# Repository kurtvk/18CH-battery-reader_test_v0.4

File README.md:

# 18CH-battery-reader_test_v0.4
18CH battery reader_test_v0.4

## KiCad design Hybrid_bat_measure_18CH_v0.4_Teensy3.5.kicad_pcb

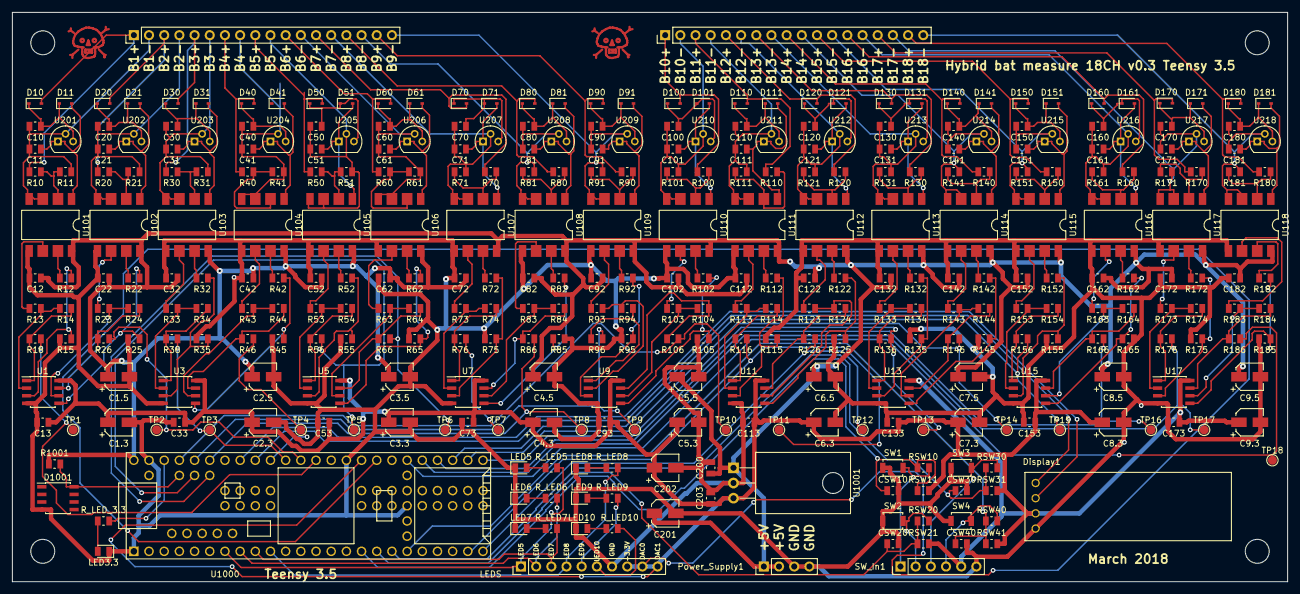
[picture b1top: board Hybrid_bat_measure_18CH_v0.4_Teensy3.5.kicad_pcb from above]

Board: 2 copper layers, 213.4 x 95.2 mm, 356 parts (0 on the bottom side), 228 nets.

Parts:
C1.3, C1.5, C2.3, C2.5, C3.3, C3.5, C4.3, C4.5, C5.3, C5.5, C6.3, C6.5, C7.3, C7.5, C8.3, C8.5, C9.3, C9.5, C201, C202: 10uF; CP_Elec_4x5.3
C10, C11, C12, C13, C20, C21, C22, C30, C31, C32, C33, C40, C41, C42, C50, C51, C52, C53, C60, C61, C62, C70, C71, C72, C73, C80, C81, C82, C90, C91, C92, C93, C100, C101, C102, C110, C111, C112, C113, C120, C121, C122, C130, C131, C132, C133, C140, C141, C142, C150, C151, C152, C153, C160, C161, C162, C170, C171, C172, C173, C180, C181, C182, C200, C203: 100n; C_0805_2012Metric
CSW10, CSW20, CSW30, CSW40: 100n; C_0805_2012Metric
D10, D11, D20, D21, D30, D31, D40, D41, D50, D51, D60, D61, D70, D71, D80, D81, D90, D91, D100, D101, D110, D111, D120, D121, D130, D131, D140, D141, D150, D151, D160, D161, D170, D171, D180, D181: D; D_SOD-323
D1001: LM385D-2.5; SOIC-8_3.9x4.9mm_P1.27mm
Display1: SSD1306; SSD1306_OLED
Inputs1, Inputs2: Conn_01x18; PinHeader_1x18_P2.54mm_Vertical
LED3.3: LED 3.3V Teensy; LED_0805_2012Metric
LED5: LED 5; LED_0805_2012Metric
LED6: LED 6; LED_0805_2012Metric
LED7: LED 7; LED_0805_2012Metric
LED8: LED 8; LED_0805_2012Metric
LED9: LED 9; LED_0805_2012Metric
LED10: LED 10; LED_0805_2012Metric
LEDS: Conn_01x10; PinHeader_1x10_P2.54mm_Vertical
MK1, MK2, MK3, MK4: Mounting_Hole_PAD; MountingHole_4mm
Power_Supply1: Conn_01x04; PinHeader_1x04_P2.54mm_Vertical
R10, R20, R30, R40, R50, R60, R70, R80, R90, R100, R110, R120, R130, R140, R150, R160, R170, R180: 15k; R_0805_2012Metric
R11, R21, R31, R41, R51, R61, R71, R81, R91, R101, R111, R121, R131, R141, R151, R161, R171, R181: 200; R_0805_2012Metric
R12, R13, R14, R15, R22, R23, R24, R25, R32, R33, R34, R35, R42, R43, R44, R45, R52, R53, R54, R55, R62, R63, R64, R65, R72, R73, R74, R75, R82, R83, R84, R85, R92, R93, R94, R95, R102, R103, R104, R105, R112, R113, R114, R115, R122, R123, R124, R125, R132, R133, R134, R135, R142, R143, R144, R145, R152, R153, R154, R155, R162, R163, R164, R165, R172, R173, R174, R175, R182, R183, R184, R185, R1001: 10k; R_0805_2012Metric
R16, R26, R36, R46, R56, R66, R76, R86, R96, R106, R116, R126, R136, R146, R156, R166, R176, R186: 1k; R_0805_2012Metric
RSW10, RSW20, RSW30, RSW40: 1k; R_0805_2012Metric
RSW11, RSW21, RSW31, RSW41: 10k; R_0805_2012Metric
R_LED5, R_LED6, R_LED7, R_LED8, R_LED9, R_LED10: 1k; R_0805_2012Metric
R_LED_3.3: 1k; R_0805_2012Metric
SKULL1, SKULL2: Symbol_Danger_CopperTop_Small
SW1, SW2, SW3, SW4: SW_Push; SW_SPST_B3U-1000P
SW_In1: Conn_01x06; PinHeader_1x06_P2.54mm_Vertical
TP1, TP2, TP3, TP4, TP5, TP6, TP7, TP8, TP9, TP10, TP11, TP12, TP13, TP14, TP15, TP16, TP17, TP18: Test Point; TestPoint_Pad_D1.5mm
U1, U3, U5, U7, U9, U11, U13, U15, U17: OPA2209; SOIC-8_3.9x4.9mm_P1.27mm
U101, U102, U103, U104, U105, U106, U107, U108, U109, U110, U111, U112, U113, U114, U115, U116, U117, U118: HCPL-7800; Fairchild_LSOP-8
U201, U202, U203, U204, U205, U206, U207, U208, U209, U210, U211, U212, U213, U214, U215, U216, U217, U218: MC78L05_TO92; TO-92
U1000: Teensy3.5; Teensy35_36
U1001: LM78_3.3; TO-220-3_Horizontal

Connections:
+3V3: C1.3.1, C2.3.1, C3.3.1, C4.3.1, C5.3.1, C6.3.1, C7.3.1, C8.3.1, C9.3.1, C13.1, C33.1, C53.1, C73.1, C93.1, C113.1, C133.1, C153.1, C173.1, C202.1, C203.1, Display1.2, LEDS.8, RSW11.2, RSW21.2, RSW31.2, RSW41.2, SW_In1.5, U1.8, U3.8, U5.8, U7.8, U9.8, U11.8, U13.8, U15.8, U17.8, U1001.3
+5V: C1.5.1, C2.5.1, C3.5.1, C4.5.1, C5.5.1, C6.5.1, C7.5.1, C8.5.1, C9.5.1, C12.1, C22.1, C32.1, C42.1, C52.1, C62.1, C72.1, C82.1, C92.1, C102.1, C112.1, C122.1, C132.1, C142.1, C152.1, C162.1, C172.1, C182.1, C200.1, C201.1, Power_Supply1.1, Power_Supply1.2, R1001.1, U101.8, U102.8, U103.8, U104.8, U105.8, U106.8, U107.8, U108.8, U109.8, U110.8, U111.8, U112.8, U113.8, U114.8, U115.8, U116.8, U117.8, U118.8, U1000.53, U1001.1
B1+: D10.2, Inputs1.1, R10.2
B1-: C10.2, C11.2, Inputs1.2, R11.1, U101.3, U101.4, U201.2
B1_output: R16.1, TP1.1, U1000.41
B2+: D20.2, Inputs1.3, R20.2
B2-: C20.2, C21.2, Inputs1.4, R21.1, U102.3, U102.4, U202.2
B2_output: R26.1, TP2.1, U1000.42
B3+: D30.2, Inputs1.5, R30.2
B3-: C30.2, C31.2, Inputs1.6, R31.1, U103.3, U103.4, U203.2
B3_output: R36.1, TP3.1, U1000.43
B4+: D40.2, Inputs1.7, R40.2
B4-: C40.2, C41.2, Inputs1.8, R41.1, U104.3, U104.4, U204.2
B4_output: R46.1, TP4.1, U1000.44
B5+: D50.2, Inputs1.9, R50.2
B5-: C50.2, C51.2, Inputs1.10, R51.1, U105.3, U105.4, U205.2
B5_output: R56.1, TP5.1, U1000.56
B6+: D60.2, Inputs1.11, R60.2
B6-: C60.2, C61.2, Inputs1.12, R61.1, U106.3, U106.4, U206.2
B6_output: R66.1, TP6.1, U1000.57
B7+: D70.2, Inputs1.13, R70.2
B7-: C70.2, C71.2, Inputs1.14, R71.1, U107.3, U107.4, U207.2
B8+: D80.2, Inputs1.15, R80.2
B8-: C80.2, C81.2, Inputs1.16, R81.1, U108.3, U108.4, U208.2
B8_output: R86.1, TP8.1, U1000.48
B9+: D90.2, Inputs1.17, R90.2
B9-: C90.2, C91.2, Inputs1.18, R91.1, U109.3, U109.4, U209.2
B9_output: R96.1, TP9.1, U1000.49
B10+: D100.2, Inputs2.1, R100.2
B10-: C100.2, C101.2, Inputs2.2, R101.1, U110.3, U110.4, U210.2
B10_output: R106.1, TP10.1, U1000.50
B11+: D110.2, Inputs2.3, R110.2
B11-: C110.2, C111.2, Inputs2.4, R111.1, U111.3, U111.4, U211.2
B11_output: R116.1, TP11.1, U1000.23
B12+: D120.2, Inputs2.5, R120.2
B12-: C120.2, C121.2, Inputs2.6, R121.1, U112.3, U112.4, U212.2
B12_output: R126.1, TP12.1, U1000.24
B13+: D130.2, Inputs2.7, R130.2
B13-: C130.2, C131.2, Inputs2.8, R131.1, U113.3, U113.4, U213.2
B13_output: R136.1, TP13.1, U1000.30
B14+: D140.2, Inputs2.9, R140.2
B14-: C140.2, C141.2, Inputs2.10, R141.1, U114.3, U114.4, U214.2
B14_output: R146.1, TP14.1, U1000.31
B15+: D150.2, Inputs2.11, R150.2
B15-: C150.2, C151.2, Inputs2.12, R151.1, U115.3, U115.4, U215.2
B15_output: R156.1, TP15.1, U1000.32
B16+: D160.2, Inputs2.13, R160.2
B16-: C160.2, C161.2, Inputs2.14, R161.1, U116.3, U116.4, U216.2
B16_output: R166.1, TP16.1, U1000.33
B17+: D170.2, Inputs2.15, R170.2
B17-: C170.2, C171.2, Inputs2.16, R171.1, U117.3, U117.4, U217.2
B17_output: R176.1, TP17.1, U1000.34
B18+: D180.2, Inputs2.17, R180.2
B18-: C180.2, C181.2, Inputs2.18, R181.1, U118.3, U118.4, U218.2
B18_output: R186.1, TP18.1, U1000.35
DAC0: LEDS.9, U1000.37
DAC1: LEDS.10, U1000.38
GND: C1.3.2, C1.5.2, C2.3.2, C2.5.2, C3.3.2, C3.5.2, C4.3.2, C4.5.2, C5.3.2, C5.5.2, C6.3.2, C6.5.2, C7.3.2, C7.5.2, C8.3.2, C8.5.2, C9.3.2, C9.5.2, C12.2, C13.2, C22.2, C32.2, C33.2, C42.2, C52.2, C53.2, C62.2, C72.2, C73.2, C82.2, C92.2, C93.2, C102.2, C112.2, C113.2, C122.2, C132.2, C133.2, C142.2, C152.2, C153.2, C162.2, C172.2, C173.2, C182.2, C200.2, C201.2, C202.2, C203.2, CSW10.2, CSW20.2, CSW30.2, CSW40.2, D1001.4, Display1.1, LED3.3.1, LED5.1, LED6.1, LED7.1, LED8.1, LED9.1, LED10.1, LEDS.7, Power_Supply1.3, Power_Supply1.4, R15.2, R25.2, R35.2, R45.2, R55.2, R65.2, R75.2, R85.1, R95.2, R105.2, R115.2, R125.2, R135.2, R145.2, R155.2, R165.1, R175.2, R185.2, SW1.1, SW2.1, SW3.1, SW4.1, SW_In1.6, U1.4, U3.4, U5.4, U7.4, U9.4, U11.4, U13.4, U15.4, U17.4, U101.5, U102.5, U103.5, U104.5, U105.5, U106.5, U107.5, U108.5, U109.5, U110.5, U111.5, U112.5, U113.5, U114.5, U115.5, U116.5, U117.5, U118.5, U1000.1, U1000.27, U1000.39, U1000.52, U1001.2
LED5: LEDS.1, R_LED5.2, U1000.7
LED6: LEDS.2, R_LED6.2, U1000.8
LED7: LEDS.3, R_LED7.2, U1000.9
LED8: LEDS.4, R_LED8.2, U1000.10
LED9: LEDS.5, R_LED9.2
LED10: LEDS.6, R_LED10.2
unnamed: C10.1, D10.1, D11.1, U201.3
unnamed: C11.1, D11.2, U101.1, U201.1
unnamed: C20.1, D20.1, D21.1, U202.3
unnamed: C21.1, D21.2, U102.1, U202.1
unnamed: C30.1, D30.1, D31.1, U203.3
unnamed: C31.1, D31.2, U103.1, U203.1
unnamed: C40.1, D40.1, U204.3
unnamed: C41.1, D41.2, U104.1, U204.1
unnamed: C50.1, D50.1, D51.1, U205.3
unnamed: C51.1, D51.2, U105.1, U205.1
unnamed: C60.1, D60.1, D61.1, U206.3
unnamed: C61.1, D61.2, U106.1, U206.1
unnamed: C70.1, D70.1, D71.1, U207.3
unnamed: C71.1, D71.2, U107.1, U207.1
unnamed: C80.1, D80.1, D81.1, U208.3
unnamed: C81.1, D81.2, U108.1, U208.1
unnamed: C90.1, D90.1, D91.1, U209.3
unnamed: C91.1, D91.2, U109.1, U209.1
unnamed: C100.1, D100.1, D101.1, U210.3
unnamed: C101.1, D101.2, U110.1, U210.1
unnamed: C110.1, D110.1, D111.1, U211.3
unnamed: C111.1, D111.2, U111.1, U211.1
unnamed: C120.1, D120.1, D121.1, U212.3
unnamed: C121.1, D121.2, U112.1, U212.1
unnamed: C130.1, D130.1, D131.1, U213.3
unnamed: C131.1, D131.2, U113.1, U213.1
unnamed: C140.1, D140.1, D141.1, U214.3
unnamed: C141.1, D141.2, U114.1, U214.1
unnamed: C150.1, D150.1, D151.1, U215.3
unnamed: C151.1, D151.2, U115.1, U215.1
unnamed: C160.1, D160.1, D161.1, U216.3
unnamed: C161.1, D161.2, U116.1, U216.1
unnamed: C170.1, D170.1, D171.1, U217.3
unnamed: C171.1, D171.2, U117.1, U217.1
unnamed: C180.1, D180.1, D181.1, U218.3
unnamed: C181.1, D181.2, U118.1, U218.1
unnamed: LED3.3.2, R_LED_3.3.1
unnamed: LED5.2, R_LED5.1
unnamed: LED6.2, R_LED6.1
unnamed: LED7.2, R_LED7.1
unnamed: LED8.2, R_LED8.1
unnamed: LED9.2, R_LED9.1
unnamed: LED10.2, R_LED10.1
unnamed: R10.1, R11.2, U101.2
unnamed: R12.1, R15.1, U1.3
unnamed: R12.2, U101.7
unnamed: R13.1, R14.2, U1.2
unnamed: R13.2, U101.6
unnamed: R14.1, R16.2, U1.1
unnamed: R20.1, R21.2, U102.2
unnamed: R22.1, R25.1, U1.5
unnamed: R22.2, U102.7
unnamed: R23.1, R24.2, U1.6
unnamed: R23.2, U102.6
unnamed: R24.1, R26.2, U1.7
unnamed: R30.1, R31.2, U103.2
unnamed: R32.1, R35.1, U3.3
unnamed: R32.2, U103.7
unnamed: R33.1, R34.2, U3.2
unnamed: R33.2, U103.6
unnamed: R34.1, R36.2, U3.1
unnamed: R40.1, R41.2, U104.2
unnamed: R42.1, R45.1, U3.5
unnamed: R42.2, U104.7
unnamed: R43.1, R44.2, U3.6
unnamed: R43.2, U104.6
unnamed: R44.1, R46.2, U3.7
unnamed: R50.1, R51.2, U105.2
unnamed: R52.1, R55.1, U5.3
unnamed: R52.2, U105.7
unnamed: R53.1, R54.2, U5.2
unnamed: R53.2, U105.6
unnamed: R54.1, R56.2, U5.1
unnamed: R60.1, R61.2, U106.2
unnamed: R62.1, R65.1, U5.5
unnamed: R62.2, U106.7
unnamed: R63.1, R64.2, U5.6
unnamed: R63.2, U106.6
unnamed: R64.1, R66.2, U5.7
unnamed: R70.1, R71.2, U107.2
unnamed: R72.1, R75.1, U7.3
unnamed: R72.2, U107.7
unnamed: R73.1, R74.2, U7.2
unnamed: R73.2, U107.6
unnamed: R74.1, R76.2, U7.1
unnamed: R76.1, TP7.1
unnamed: R80.1, R81.2, U108.2
unnamed: R82.1, R85.2, U7.5
unnamed: R82.2, U108.7
unnamed: R83.1, R84.2, U7.6
unnamed: R83.2, U108.6
unnamed: R84.1, R86.2, U7.7
unnamed: R90.1, R91.2, U109.2
unnamed: R92.1, R95.1, U9.3
unnamed: R92.2, U109.7
unnamed: R93.1, R94.2, U9.2
unnamed: R93.2, U109.6
unnamed: R94.1, R96.2, U9.1
unnamed: R100.1, R101.2, U110.2
unnamed: R102.1, R105.1, U9.5
unnamed: R102.2, U110.7
unnamed: R103.1, R104.2, U9.6
unnamed: R103.2, U110.6
unnamed: R104.1, R106.2, U9.7
unnamed: R110.1, R111.2, U111.2
unnamed: R112.1, R115.1, U11.3
unnamed: R112.2, U111.7
unnamed: R113.1, R114.2, U11.2
unnamed: R113.2, U111.6
unnamed: R114.1, R116.2, U11.1
unnamed: R120.1, R121.2, U112.2
unnamed: R122.1, R125.1, U11.5
unnamed: R122.2, U112.7
unnamed: R123.1, R124.2, U11.6
unnamed: R123.2, U112.6
unnamed: R124.1, R126.2, U11.7
unnamed: R130.1, R131.2, U113.2
unnamed: R132.1, R135.1, U13.3
unnamed: R132.2, U113.7
unnamed: R133.1, R134.2, U13.2
unnamed: R133.2, U113.6
unnamed: R134.1, R136.2, U13.1
unnamed: R140.1, R141.2, U114.2
unnamed: R142.1, R145.1, U13.5
unnamed: R142.2, U114.7
unnamed: R143.1, R144.2, U13.6
unnamed: R143.2, U114.6
unnamed: R144.1, R146.2, U13.7
unnamed: R150.1, R151.2, U115.2
unnamed: R152.1, R155.1, U15.3
unnamed: R152.2, U115.7
unnamed: R153.1, R154.2, U15.2
unnamed: R153.2, U115.6
unnamed: R154.1, R156.2, U15.1
unnamed: R160.1, R161.2, U116.2
unnamed: R162.1, R165.2, U15.5
unnamed: R162.2, U116.7
unnamed: R163.1, R164.2, U15.6
unnamed: R163.2, U116.6
unnamed: R164.1, R166.2, U15.7
unnamed: R170.1, R171.2, U117.2
unnamed: R172.1, R175.1, U17.3
unnamed: R172.2, U117.7
unnamed: R173.1, R174.2, U17.2
unnamed: R173.2, U117.6
unnamed: R174.1, R176.2, U17.1
unnamed: R180.1, R181.2, U118.2
unnamed: R182.1, R185.1, U17.5
unnamed: R182.2, U118.7
unnamed: R183.1, R184.2, U17.6
unnamed: R183.2, U118.6
unnamed: R184.1, R186.2, U17.7
unnamed: R_LED_3.3.2, U1000.51
SCL_OLED: Display1.3, U1000.46
SDA_OLED: Display1.4, U1000.45
SW1: CSW10.1, RSW10.1, RSW11.1, U1000.16
SW1_IN: RSW10.2, SW1.2, SW_In1.1
SW2: CSW20.1, RSW20.1, RSW21.1, U1000.17
SW2_IN: RSW20.2, SW2.2, SW_In1.2
SW3: CSW30.1, RSW30.1, RSW31.1, U1000.18
SW3_IN: RSW30.2, SW3.2, SW_In1.3
SW4: CSW40.1, RSW40.1, RSW41.1, U1000.19
SW4_IN: RSW40.2, SW4.2, SW_In1.4
VRef2.5: D1001.8, R1001.2, U1000.55
